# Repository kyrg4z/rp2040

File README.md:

# RP2040 Devboard with OLED

## About 

This repository documents my first PCB hardware project. 

The goal was not to create a completely original product but to understand how to develop one. 

I wanted to learn how devboards are designed, study each subsystem and make small modifications. 

Through this project I learned:

- Kicad workflow 
- schematic design
- PCB layouts
- design rules (DRC/ERC) & how to resolve them
- USB connections 
- power distribution 
- decoupling 
- I²C communication
- datasheets 
- adding an OLED display 

## Inspiration

The original inspiration came from Kai Pereira's RP2040 development board and accompanying tutorial.

## What I Changed

- Added an OLED display connected over I²C
- Minor routing/layout changes
- Learned how to resolve DRC issues
- Explored footprint selection and placement

## Current Status

✔ Schematic complete

✔ PCB routed

✔ DRC passes

❌ Board not manufactured yet

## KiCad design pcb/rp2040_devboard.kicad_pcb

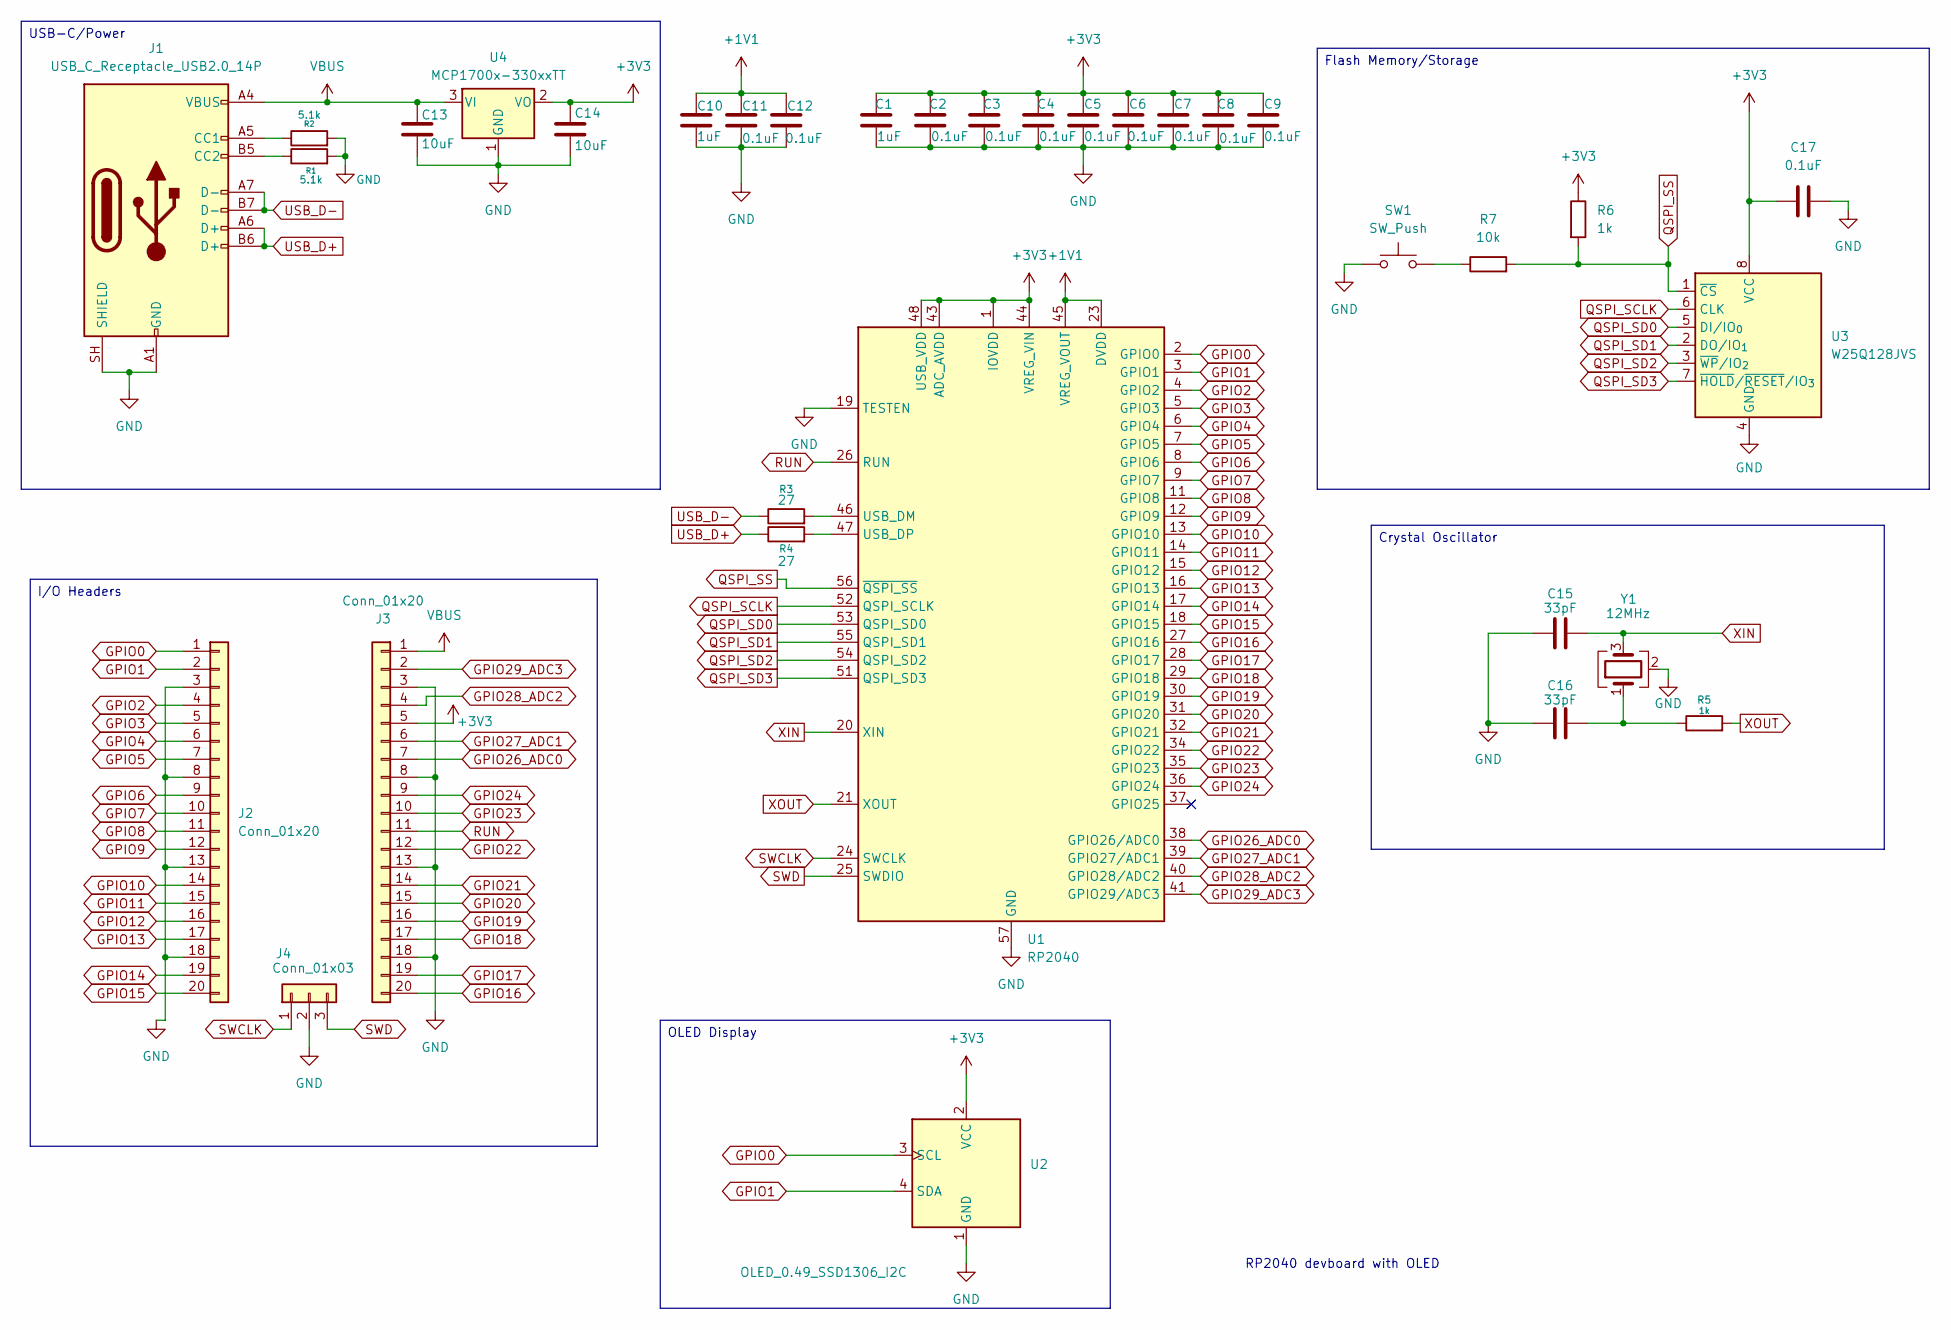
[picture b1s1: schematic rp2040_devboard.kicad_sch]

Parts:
C1, C10: 1uF; C_0402_1005Metric
C2, C3, C4, C5, C6, C7, C8, C9, C11, C12, C17: 0.1uF; C_0402_1005Metric
C13, C14: 10uF; C_0603_1608Metric
C15, C16: 33pF; C_0402_1005Metric
J1: USB_C_Receptacle_USB2.0_14P; USB_C_Receptacle_HRO_TYPE-C-31-M-12
J2, J3: Conn_01x20; PinHeader_1x20_P2.54mm_Vertical
J4: Conn_01x03; PinHeader_1x03_P2.54mm_Vertical
R1, R2: 5.1k; R_0402_1005Metric
R3, R4: 27; R_0402_1005Metric
R5, R6: 1k; R_0402_1005Metric
R7: 10k; R_0402_1005Metric
SW1: SW_Push; SW_Push_SPST_NO_Alps_SKRK
U1: RP2040; QFN-56-1EP_7x7mm_P0.4mm_EP3.2x3.2mm
U2: OLED_0.49_SSD1306_I2C; ER_OLEDM0.91_1x-I2C
U3: W25Q128JVS; Winbond_USON-8-1EP_3x2mm_P0.5mm_EP0.2x1.6mm
U4: MCP1700x-330xxTT; SOT-23
Y1: 12MHz; Crystal_SMD_3225-4Pin_3.2x2.5mm

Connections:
+1V1: C10.1, C11.1, C12.1, U1.23 (DVDD), U1.45 (VREG_VOUT), U1.50 (DVDD)
+3V3: C1.1, C2.1, C3.1, C4.1, C5.1, C6.1, C7.1, C8.1, C9.1, C14.1, C17.2, J3.5, R6.1, U1.1 (IOVDD), U1.10 (IOVDD), U1.22 (IOVDD), U1.33 (IOVDD), U1.42 (IOVDD), U1.43 (ADC_AVDD), U1.44 (VREG_VIN), U1.48 (USB_VDD), U1.49 (IOVDD), U2.2 (VCC), U3.8 (VCC), U4.2 (VO)
GND: C1.2, C2.2, C3.2, C4.2, C5.2, C6.2, C7.2, C8.2, C9.2, C10.2, C11.2, C12.2, C13.2, C14.2, C15.1, C16.1, C17.1, J1.A1 (GND), J1.A12 (GND), J1.B1 (GND), J1.B12 (GND), J1.SH (SHIELD), J2.3, J2.8, J2.13, J2.18, J3.3, J3.8, J3.13, J3.18, J4.2, R1.2, R2.2, SW1.1, U1.19 (TESTEN), U1.57 (GND), U2.1 (GND), U3.4 (GND), U4.1 (GND), Y1.2 (G), Y1.4 (G)
GPIO0: J2.1, U1.2 (GPIO0), U2.3 (SCL)
GPIO1: J2.2, U1.3 (GPIO1), U2.4 (SDA)
GPIO2: J2.4, U1.4 (GPIO2)
GPIO3: J2.5, U1.5 (GPIO3)
GPIO4: J2.6, U1.6 (GPIO4)
GPIO5: J2.7, U1.7 (GPIO5)
GPIO6: J2.9, U1.8 (GPIO6)
GPIO7: J2.10, U1.9 (GPIO7)
GPIO8: J2.11, U1.11 (GPIO8)
GPIO9: J2.12, U1.12 (GPIO9)
GPIO10: J2.14, U1.13 (GPIO10)
GPIO11: J2.15, U1.14 (GPIO11)
GPIO12: J2.16, U1.15 (GPIO12)
GPIO13: J2.17, U1.16 (GPIO13)
GPIO14: J2.19, U1.17 (GPIO14)
GPIO15: J2.20, U1.18 (GPIO15)
GPIO16: J3.20, U1.27 (GPIO16)
GPIO17: J3.19, U1.28 (GPIO17)
GPIO18: J3.17, U1.29 (GPIO18)
GPIO19: J3.16, U1.30 (GPIO19)
GPIO20: J3.15, U1.31 (GPIO20)
GPIO21: J3.14, U1.32 (GPIO21)
GPIO22: J3.12, U1.34 (GPIO22)
GPIO23: J3.10, U1.35 (GPIO23)
GPIO24: J3.9, U1.36 (GPIO24)
GPIO26_ADC0: J3.7, U1.38 (GPIO26/ADC0)
GPIO27_ADC1: J3.6, U1.39 (GPIO27/ADC1)
GPIO28_ADC2: J3.4, U1.40 (GPIO28/ADC2)
GPIO29_ADC3: J3.2, U1.41 (GPIO29/ADC3)
unnamed: C16.2, R5.1, Y1.1
unnamed: J1.A5 (CC1), R2.1
unnamed: J1.B5 (CC2), R1.1
unnamed: R7.1, SW1.2
unnamed: R3.2, U1.46 (USB_DM)
unnamed: R4.2, U1.47 (USB_DP)
QSPI_SCLK: U1.52 (QSPI_SCLK), U3.6 (CLK)
QSPI_SD0: U1.53 (QSPI_SD0), U3.5 (DI/IO_{0})
QSPI_SD1: U1.55 (QSPI_SD1), U3.2 (DO/IO_{1})
QSPI_SD2: U1.54 (QSPI_SD2), U3.3 (~WP/IO_{2})
QSPI_SD3: U1.51 (QSPI_SD3), U3.7 (~HOLD/~RESET/IO_{3})
QSPI_SS: R6.2, R7.2, U1.56 (~QSPI_SS), U3.1 (~CS)
RUN: J3.11, U1.26 (RUN)
SWCLK: J4.1, U1.24 (SWCLK)
SWD: J4.3, U1.25 (SWDIO)
USB_D+: J1.A6 (D+), J1.B6 (D+), R4.1
USB_D-: J1.A7 (D-), J1.B7 (D-), R3.1
VBUS: C13.1, J1.A4 (VBUS), J1.A9 (VBUS), J1.B4 (VBUS), J1.B9 (VBUS), J3.1, U4.3 (VI)
XIN: C15.2, U1.20 (XIN), Y1.3
XOUT: R5.2, U1.21 (XOUT)

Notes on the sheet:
RP2040 devboard with OLED
I/O Headers
Crystal Oscillator
Flash Memory/Storage
USB-C/Power
OLED Display

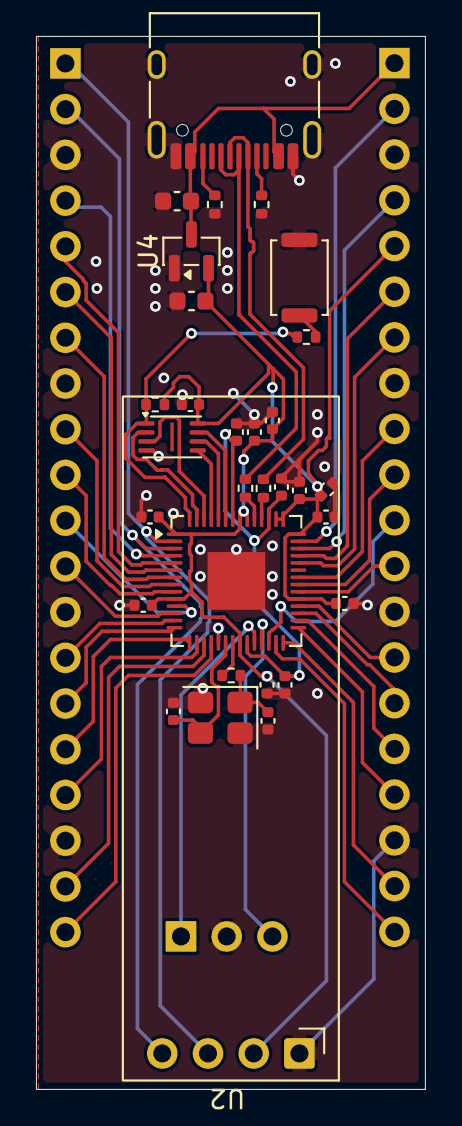
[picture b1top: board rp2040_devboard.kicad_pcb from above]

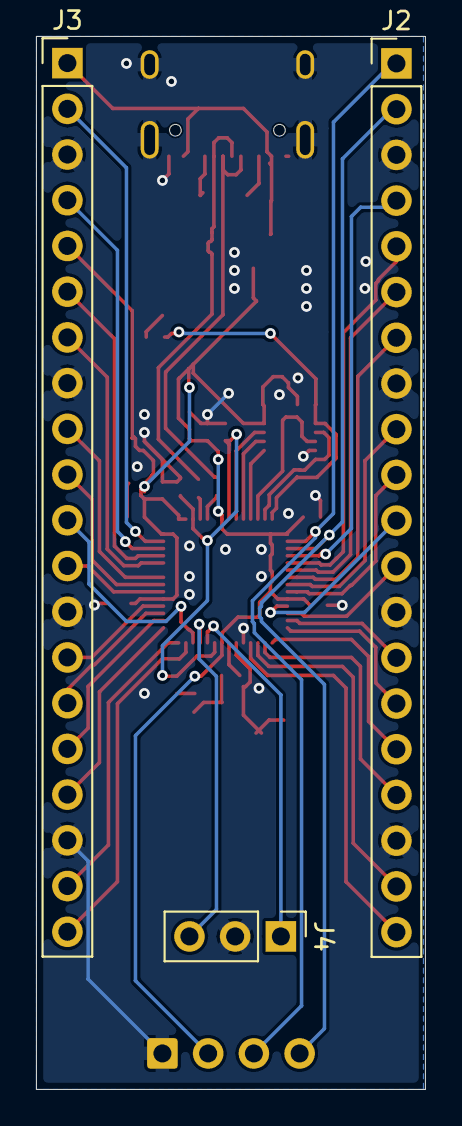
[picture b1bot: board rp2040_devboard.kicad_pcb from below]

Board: 2 copper layers, 21.6 x 58.5 mm, 34 parts (3 on the bottom side), 52 nets.

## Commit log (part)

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2026-05-05 first commit, starting the schematic
2026-05-06 USB-C created and added couple of global labels
2026-05-07 Added crystal oscilator to the schematic
